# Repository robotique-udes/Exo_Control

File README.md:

# Exo_Control - ACE 2026

## Table of Contents

- [Our Team](#our-team)
- [Description](#description)
- [Project Overview](#project-overview)
- [Hardware](#hardware)
- [Getting Started](#getting-started)
- [Folder Overview](#folder-overview)
- [Development Notes](#development-notes)
- [License](#license)
- [Acknowledgments](#acknowledgments)
- [Authors](#authors)

## Our Team

## Description

**BioGenius** is a technical project within the Robotique UdeS group focused on designing a lightweight and powerful exoskeleton system. This system provides support to the legs, hips, and back, making walking and load handling easier. Our prototype helped the team secure first place at the Applied Collegiate Exoskeleton (ACE) Competition in the United States in both 2022 and 2023.

Founded in the fall of 2019 by two bioengineering enthusiasts, BioGenius has grown into a team of more than 10 members with expertise from several engineering disciplines. This project represents a pioneering effort at the undergraduate engineering level in Quebec.

This release corresponds to the code used for the **ACE 2026** competition at McMaster University.

<div style="text-align: center;">
  
</div>

## Hardware

The system is built around the following main hardware components:

- Microcontroller: Arduino ESP32 nano
- Inertial Measurement Units: BNO085
- Motor: CubemarsV2 AK10-9 KV100 and V3 AK10-9 KV60

## Getting Started

To get started with the project, clone the repository and build it with PlatformIO.

```bash
git clone https://github.com/robotique-udes/Exo_Control.git
cd Exo_Control
pio run
pio run -t upload
```

## Folder Overview

- [include](include): header files, class declarations, and shared configuration definitions
- [src](src): implementation files for the firmware, sensor handling, control logic, and motor control
- [docs](docs): development guidelines and supporting documentation
- [test](test): test-related files and future validation work
- [platformio.ini](platformio.ini): PlatformIO configuration for the embedded build

## Development Notes

The project follows the coding conventions documented in [docs/guideline/code_guideline.md](docs/guideline/code_guideline.md). In particular:

- use clear and descriptive names
- keep the code structure consistent
- document headers with Doxygen comments
- separate configuration, logic, and hardware interface concerns clearly

## License

Copyright (C) 2026,  Robotique UdeS

This program is free software: you can redistribute it and/or modify
it under the terms of the GNU General Public License as published by
the Free Software Foundation, either version 3 of the License, or
(at your option) any later version.

This program is distributed in the hope that it will be useful,
but WITHOUT ANY WARRANTY; without even the implied warranty of
MERCHANTABILITY or FITNESS FOR A PARTICULAR PURPOSE. See the
GNU General Public License for more details.

For more details, see <https://www.gnu.org/licenses/>.

## Acknowledgments

We invite you to explore the [Robotique UdeS website](https://robotiqueudes.ca/) to learn more about the team and discover other projects.

## Authors

The main contributors to the Exo_Control project are:

- Gabriel Desrochers
- Josseran-Pierre Gay
- Eloi Charbonneau
- Samuel Savaria
- Samuel Archambault
- Halima Bourdi
- Reem Youssef
- Édouard Moffet
- Jacob Turcotte
- Dannick Bilodeau
- Simon Trudeau
- Jorand Gagnon

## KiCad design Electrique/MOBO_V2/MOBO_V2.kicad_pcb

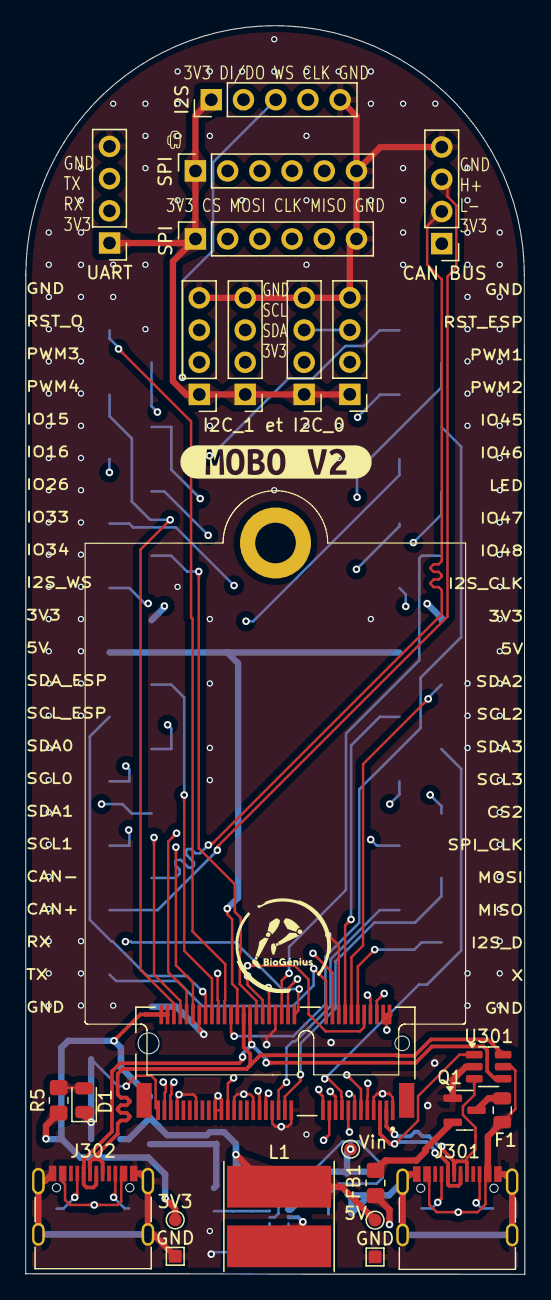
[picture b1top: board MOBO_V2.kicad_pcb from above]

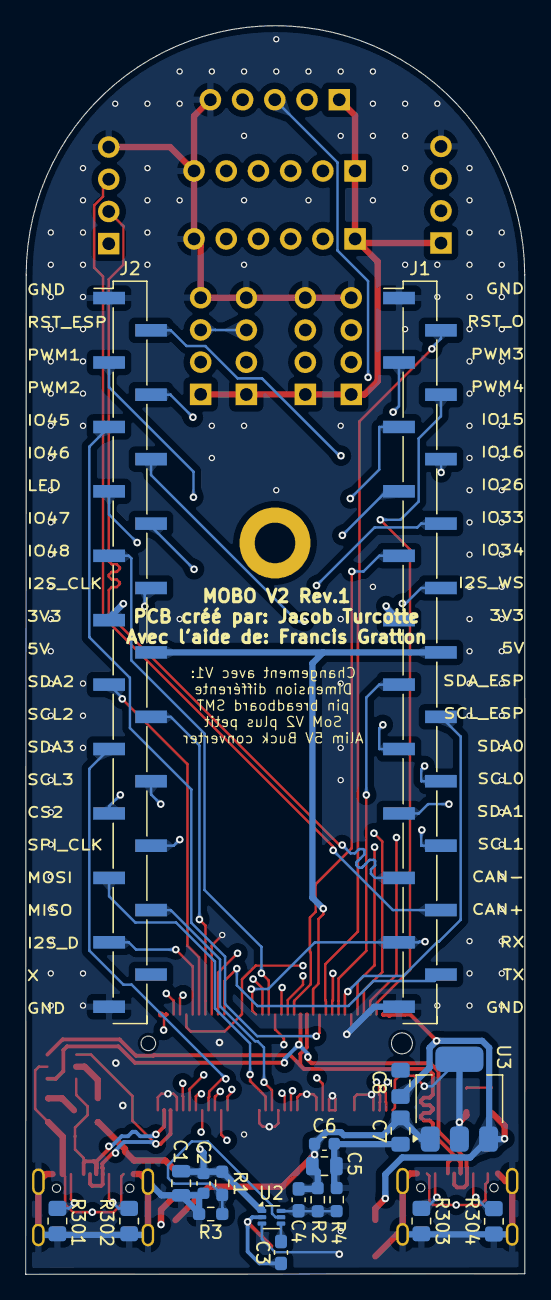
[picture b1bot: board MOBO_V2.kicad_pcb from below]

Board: 4 copper layers, 39.4 x 98.5 mm, 45 parts (20 on the bottom side), 58 nets.

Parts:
3V3: TP_3v3; TestPoint_Pad_D1.0mm
5V: TP_5V; TestPoint_Pad_D1.0mm
C1: 10µF; C_0805_2012Metric
C2, C6: 0,1µF; C_0603_1608Metric
C3: 0,1µF; C_0603_1608Metric_Pad1.08x0.95mm_HandSolder
C4: 33pF; C_0603_1608Metric_Pad1.08x0.95mm_HandSolder
C5: 22µF; C_0805_2012Metric
C7, C8: 4,7µF; C_0805_2012Metric_Pad1.18x1.45mm_HandSolder
CAN BUS: CAN_BUS; PinHeader_1x04_P2.54mm_Vertical
D1: Green_power; D_0805_2012Metric
F1: SMD0805B110TF; Fuse_0805_2012Metric
FB1: 600 @ 100MHz; R_0805_2012Metric_Pad1.20x1.40mm_HandSolder
GND: TP_GND; TestPoint_Pad_1.0x1.0mm
GND#2: TP_GND_IN; TestPoint_Pad_1.0x1.0mm
I2S: I2S; PinHeader_1x05_P2.54mm_Vertical
J1: Gauche; PinHeader_1x23_P2.54mm_Vertical_SMD_Pin1Left
J2: Droite; PinHeader_1x23_P2.54mm_Vertical_SMD_Pin1Left
J301: USB_C_UART; USB_C_Receptacle_G-Switch_GT-USB-7010ASV
J302: USB_C_DEBUG; USB_C_Receptacle_G-Switch_GT-USB-7010ASV
J307: I2C_0_0; PinHeader_1x04_P2.54mm_Vertical
J308: I2C_0_1; PinHeader_1x04_P2.54mm_Vertical
J309: I2C_1_0; PinHeader_1x04_P2.54mm_Vertical
J310: I2C_1_1; PinHeader_1x04_P2.54mm_Vertical
L1: 3,3µH 20mOhm; L_TDK_VLP8040
Q1: AO3401A; SOT-23
R1: 100k; R_0603_1608Metric_Pad0.98x0.95mm_HandSolder
R2: 158k; R_0603_1608Metric_Pad0.98x0.95mm_HandSolder
R3: 28k; R_0603_1608Metric_Pad0.98x0.95mm_HandSolder
R4: 30k; R_0603_1608Metric_Pad0.98x0.95mm_HandSolder
R5: 330; R_0805_2012Metric_Pad1.20x1.40mm_HandSolder
R301, R302, R303, R304: 5.1k; R_0805_2012Metric_Pad1.20x1.40mm_HandSolder
SPI: Conn_SPI; PinSocket_1x06_P2.54mm_Vertical
SPI#2: Conn_Module_SD; PinSocket_1x06_P2.54mm_Vertical
U1: AMPHENOL_MDT320E01001
U2: TPS562242DRLR; SOT-563
U3: AP7361C-33E; SOT-223-3_TabPin2
U301: SRV05-4; SOT-23-6
UART: UART; PinHeader_1x04_P2.54mm_Vertical
Vin: TP_VIN; TestPoint_Pad_D1.0mm
kibuzzard-66E82988: G***; kibuzzard-66E82988

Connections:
CAN_N: CAN BUS.2, J1.19, U1.73 (CAN_L_MCP2515)
CAN_P: CAN BUS.3, J1.20, U1.71 (CAN_H_MCP2515)
CHIP_EN: J2.2, U1.56 (RESET_ESP32)
CS_1: SPI#2.2, U1.20 (CS_1)
CS_2: J2.17, SPI.2, U1.21 (CS_2)
DEBUG_D+: J302.A6 (D+), J302.B6 (D+), U1.48 (USB_DEBUG_D+), U301.6 (IO4)
DEBUG_D-: J302.A7 (D-), J302.B7 (D-), U1.46 (USB_DEBUG_D-), U301.4 (IO3)
FT231_D+: J301.A6 (D+), J301.B6 (D+), U1.3 (USB_D+_FT231), U301.3 (IO2)
FT231_D-: J301.A7 (D-), J301.B7 (D-), U1.5 (USB_D-_FT231), U301.1 (IO1)
GND: C1.2, C2.2, C5.2, C6.2, C7.1, C8.1, CAN BUS.4, D1.1 (K), GND.1, GND#2.1, I2S.5, J1.1, J1.23, J2.1, J2.23, J301.A1 (GND), J301.A12 (GND), J301.B1 (GND), J301.B12 (GND), J301.S1 (SHIELD), J302.A1 (GND), J302.A12 (GND), J302.B1 (GND), J302.B12 (GND), J302.S1 (SHIELD), J307.4, J308.4, J309.4, J310.4, Q1.1 (G), R3.2, R4.2, R301.2, R302.2, R303.2, R304.2, SPI.6, SPI#2.6, U1.1 (GND), U1.7 (GND), U1.18 (GND), U1.33 (GND), U1.38 (GND), U1.39 (GND), U1.45 (GND), U1.51 (GND), U1.55 (GND), U1.57 (GND), U1.62 (GND), U1.63 (GND), U1.69 (GND), U1.75 (GND), U2.3 (GND), U3.2 (GND), U301.2 (VN), UART.4
GPIO15: J1.5, U1.40 (GPIO15)
GPIO16: J1.6, U1.41 (GPIO16)
GPIO17_U1_TXD: J1.22, U1.22 (UART_TX), UART.3
GPIO18_U1_RXD: J1.21, U1.32 (UART_RX), UART.2
GPIO26: J1.7, U1.42 (GPIO26)
GPIO33: J1.8, U1.43 (GPIO33)
GPIO34: J1.9, U1.44 (GPIO34)
GPIO38_ADDRESSABLE_LED: J2.7, U1.6 (GPIO38&LED)
GPIO45: J2.5, U1.52 (GPIO45)
GPIO46: J2.6, U1.53 (GPIO46)
GPIO47: J2.8, U1.34 (RST_OTHER)
GPIO48/CAN_INT: J2.9, U1.36 (GPIO48)
I2C_SCL_0_TCA: J1.16, J307.3, J308.3, U1.11 (I2C_SCL_1_TCA)
I2C_SCL_1_TCA: J1.18, J309.3, J310.3, U1.15 (I2C_SCL_2_TCA)
I2C_SCL_2_TCA: J2.14, U1.16 (I2C_SCL_3_TCA)
I2C_SCL_3_TCA: J2.16, U1.19 (I2C_SCL_4_TCA)
I2C_SCL_ESP32: J1.14, U1.60 (I2C_SCL_ESP32)
I2C_SDA_0_TCA: J1.15, J307.2, J308.2, U1.9 (I2C_SDA_1_TCA)
I2C_SDA_1_TCA: J1.17, J309.2, J310.2, U1.13 (I2C_SDA_2_TCA)
I2C_SDA_2_TCA: J2.13, U1.14 (I2C_SDA_3_TCA)
I2C_SDA_3_TCA: J2.15, U1.17 (I2C_SDA_4_TCA)
I2C_SDA_ESP32: J1.13, U1.58 (I2C_SDA_ESP32)
I2S_BCLK: I2S.4, J2.10, U1.8 (I2S_BCLK)
I2S_DIN/DOUT: I2S.2, J2.21, U1.12 (I2S_DIN/DOUT)
I2S_WS: I2S.3, J1.10, U1.10 (I2S_WS)
unnamed: D1.2 (A), R5.2
unnamed: J301.A5 (CC1), R302.1
unnamed: J301.B5 (CC2), R301.1
unnamed: J302.A5 (CC1), R304.1
unnamed: J302.B5 (CC2), R303.1
unnamed: F1.2, Q1.3 (D)
unnamed: FB1.1, Q1.2 (S)
unnamed: R1.2, R3.1, U2.5 (EN)
unnamed: C3.1, L1.1, U2.2 (SW)
unnamed: C3.2, U2.4 (VBST)
unnamed: C4.2, R2.2, R4.1, U2.6 (VFB)
PWM_1: J2.3, U1.64 (PWM_1_PCA)
PWM_2: J2.4, U1.66 (PWM_2_PCA)
PWM_3: J1.3, U1.68 (PWM_3_PCA)
PWM_4: J1.4, U1.70 (PWM_4_PCA)
RESET_OTHERS: J1.2, U1.54 (RESET_AUTRES)
SPI_CLK_ESP32: J2.18, SPI.4, SPI#2.4, U1.23 (SPI_CLK)
SPI_MISO_ESP32: J2.20, SPI.5, SPI#2.5, U1.37 (SPI_MISO)
SPI_MOSI_ESP32: J2.19, SPI.3, SPI#2.3, U1.35 (SPI_MOSI)
VBUS: F1.1, J301.A4 (VBUS), J301.A9 (VBUS), J301.B4 (VBUS), J301.B9 (VBUS), J302.A4 (VBUS), J302.A9 (VBUS), J302.B4 (VBUS), J302.B9 (VBUS), U301.5 (VP)
VIN_PROTECTION: C1.1, C2.1, FB1.2, R1.1, U2.1 (VIN), Vin.1
Vcc_3V3: 3V3.1, C8.2, CAN BUS.1, I2S.1, J1.11, J2.11, J307.1, J308.1, J309.1, J310.1, R5.1, SPI.1, SPI#2.1, U1.2 (Vcc_3v3), U1.4 (Vcc_3v3), U1.72 (Vcc_3v3), U1.74 (Vcc_3v3), U3.3 (VO), UART.1
Vcc_5V: 5V.1, C4.1, C5.1, C6.1, C7.2, J1.12, J2.12, L1.2, R2.1, U1.50 (Vcc_5V), U3.1 (VI)

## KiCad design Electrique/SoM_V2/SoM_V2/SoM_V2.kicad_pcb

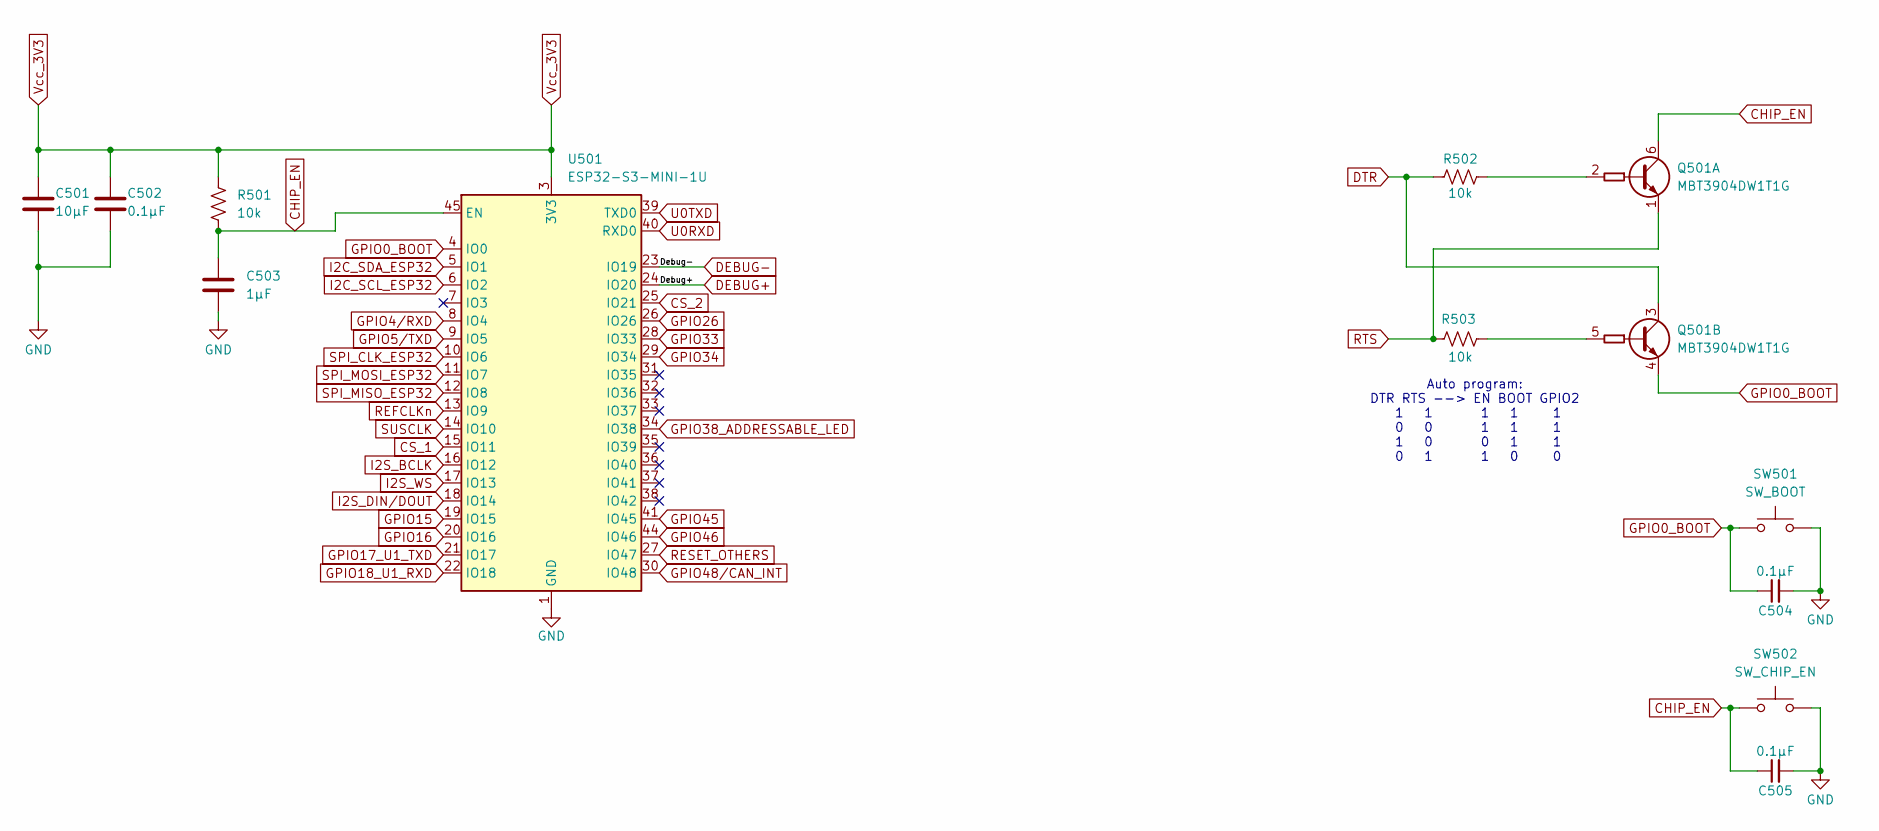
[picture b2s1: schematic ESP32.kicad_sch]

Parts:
C501: 10µF; R_0805_2012Metric
C502, C504, C505: 0.1µF; R_0805_2012Metric
C503: 1µF; R_0805_2012Metric
Q501: MBT3904DW1T1G; SOT-363_SC-70-6
R501, R502, R503: 10k; R_0805_2012Metric
SW501: SW_BOOT; SW_DIP_SPSTx01_Slide_6.7x4.1mm_W6.73mm_P2.54mm_LowProfile_J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
SW502: SW_CHIP_EN; SW_DIP_SPSTx01_Slide_6.7x4.1mm_W6.73mm_P2.54mm_LowProfile_J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
U501: ESP32-S3-MINI-1U; ESP32-S2-MINI-1U

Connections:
CHIP_EN: C503.1, C505.1, Q501.6 (C1), R501.2, SW502.1, U501.45 (EN); also elsewhere on the board
CS_1: U501.15 (IO11); also elsewhere on the board
CS_2: U501.25 (IO21); also elsewhere on the board
DEBUG+: U501.24 (IO20); also elsewhere on the board
DEBUG-: U501.23 (IO19); also elsewhere on the board
DTR: Q501.3 (C2), R502.1; also elsewhere on the board
GPIO0_BOOT: C504.1, Q501.4 (E2), SW501.1, U501.4 (IO0)
GPIO4/RXD: U501.8 (IO4); also elsewhere on the board
GPIO5/TXD: U501.9 (IO5); also elsewhere on the board
GPIO15: U501.19 (IO15); also elsewhere on the board
GPIO16: U501.20 (IO16); also elsewhere on the board
GPIO17_U1_TXD: U501.21 (IO17); also elsewhere on the board
GPIO18_U1_RXD: U501.22 (IO18); also elsewhere on the board
GPIO26: U501.26 (IO26); also elsewhere on the board
GPIO33: U501.28 (IO33); also elsewhere on the board
GPIO34: U501.29 (IO34); also elsewhere on the board
GPIO38_ADDRESSABLE_LED: U501.34 (IO38); also elsewhere on the board
GPIO45: U501.41 (IO45); also elsewhere on the board
GPIO46: U501.44 (IO46); also elsewhere on the board
GPIO48/CAN_INT: U501.30 (IO48); also elsewhere on the board
I2C_SCL_ESP32: U501.6 (IO2); also elsewhere on the board
I2S_BCLK: U501.16 (IO12); also elsewhere on the board
I2S_DIN/DOUT: U501.18 (IO14); also elsewhere on the board
I2S_WS: U501.17 (IO13); also elsewhere on the board
unnamed: Q501.2 (B1), R502.2
unnamed: Q501.5 (B2), R503.2
REFCLKn: U501.13 (IO9)
RESET_OTHERS: U501.27 (IO47); also elsewhere on the board
RTS: Q501.1 (E1), R503.1; also elsewhere on the board
SPI_CLK_ESP32: U501.10 (IO6); also elsewhere on the board
SPI_MISO_ESP32: U501.12 (IO8); also elsewhere on the board
SPI_MOSI_ESP32: U501.11 (IO7); also elsewhere on the board
SUSCLK: U501.14 (IO10)
U0RXD: U501.40 (RXD0); also elsewhere on the board
U0TXD: U501.39 (TXD0); also elsewhere on the board

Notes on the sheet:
Auto program: DTR RTS --> EN BOOT GPIO2 1 1 1 1 1 0 0 1 1 1 1 0 0 1 1 0 1 1 0 0

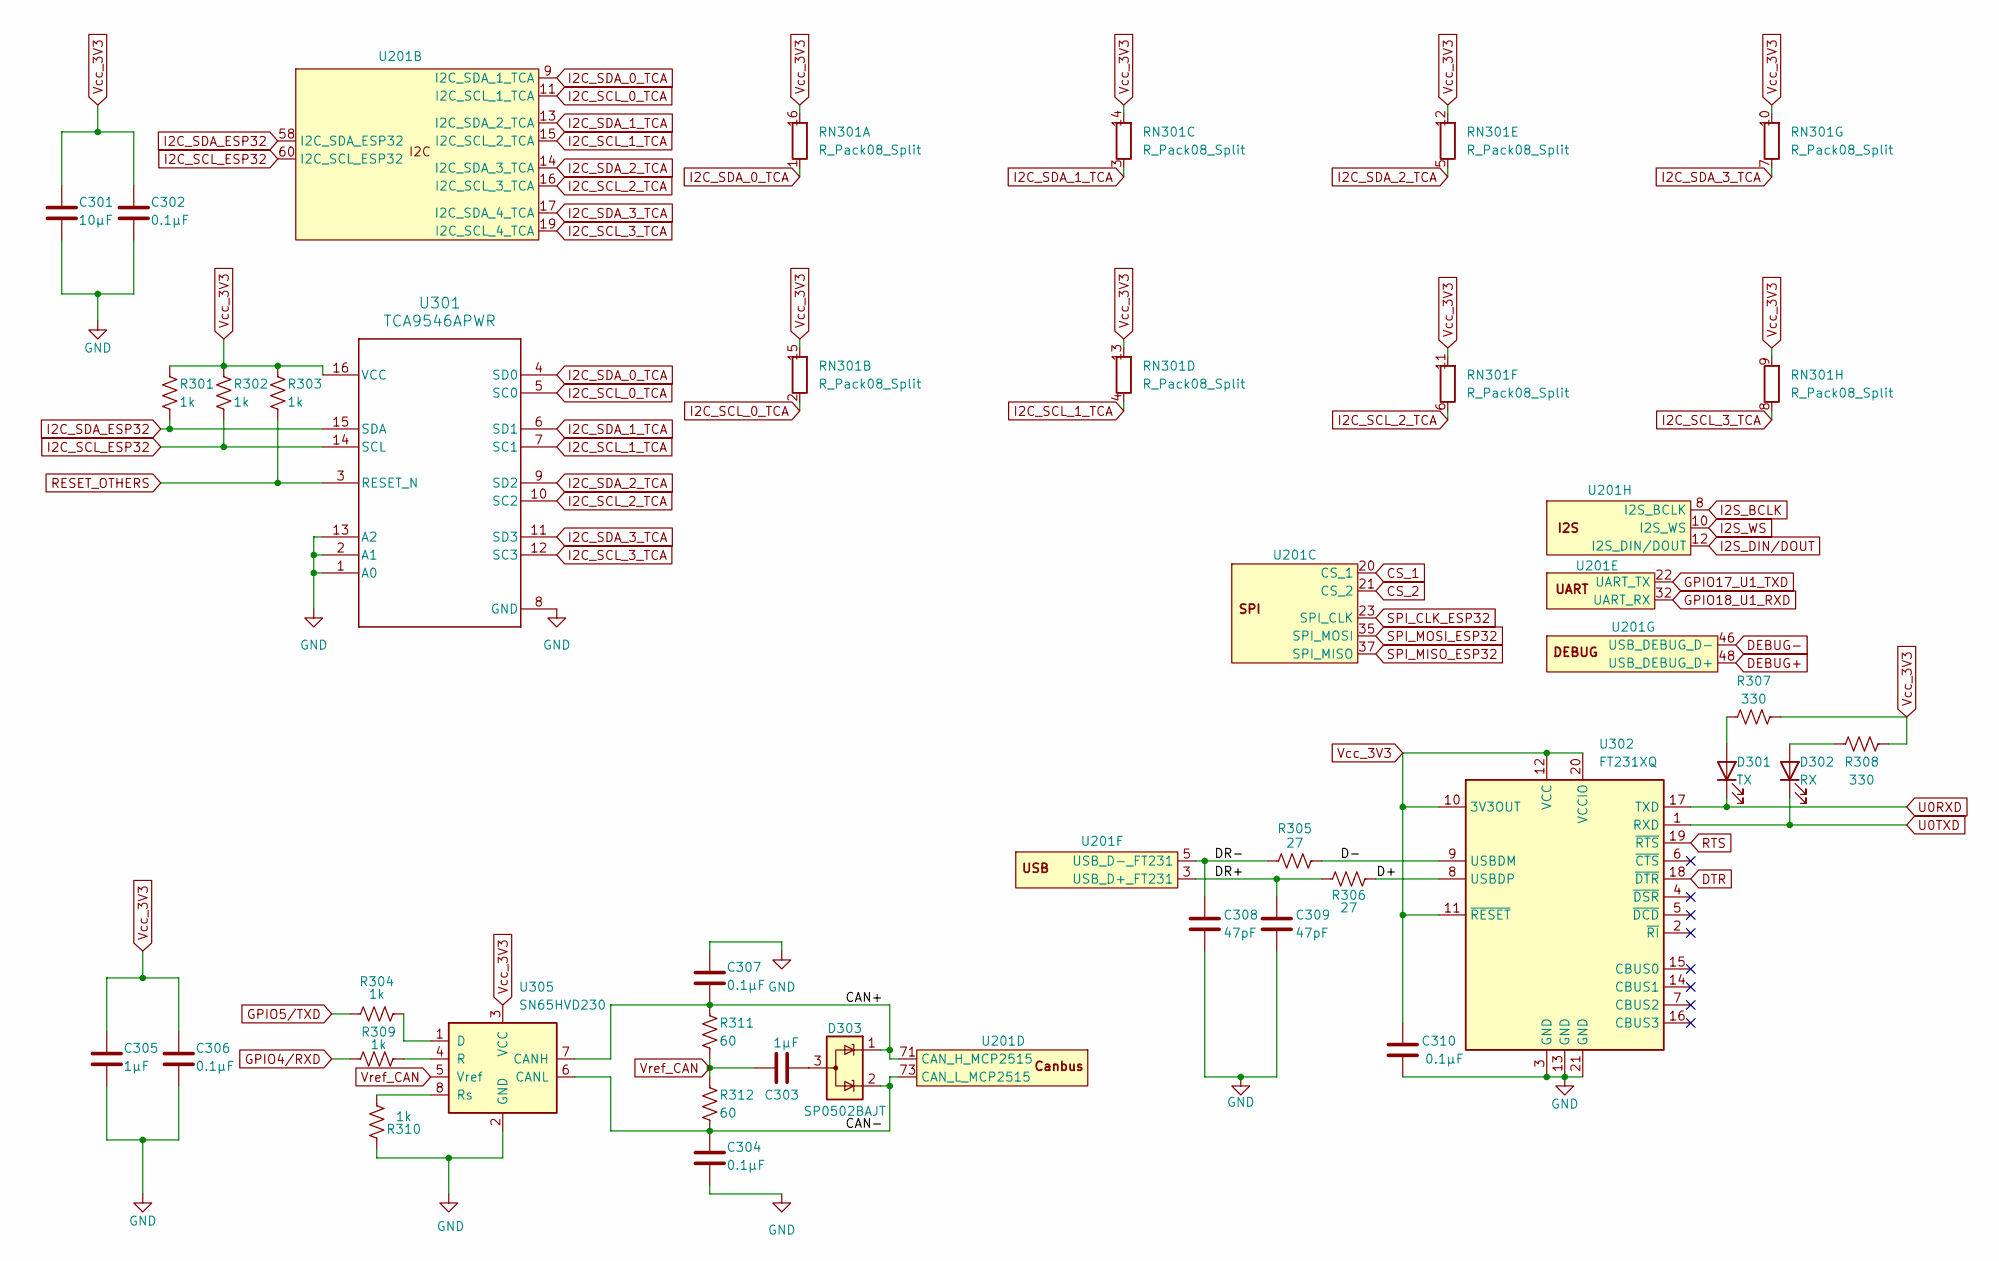
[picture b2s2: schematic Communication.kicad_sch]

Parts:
C301: 10µF; R_0805_2012Metric
C302, C304, C306, C307, C310: 0.1µF; R_0805_2012Metric
C303, C305: 1µF; R_0805_2012Metric
C308, C309: 47pF; R_0805_2012Metric
D301: TX; LED_0805_2012Metric
D302: RX; LED_0805_2012Metric
D303: SP0502BAJT; SOT-323_SC-70
R301, R302, R303, R304, R309, R310: 1k; R_0805_2012Metric
R305, R306: 27; R_0805_2012Metric
R307, R308: 330; R_0805_2012Metric
R311, R312: 60; R_0805_2012Metric
RN301: R_Pack08_Split; R_Array_Convex_8x0602
U201: NGFF_E
U301: TCA9546APWR; TSSOP-16_4.4x5mm_P0.65mm
U302: FT231XQ; QFN-20-1EP_4x4mm_P0.5mm_EP2.5x2.5mm
U305: SN65HVD230; SOIC-8_3.9x4.9mm_P1.27mm

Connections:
/Communication/CAN+: C307.2, D303.1 (K), R311.1, U201.71 (CAN_H_MCP2515), U305.7 (CANH)
/Communication/CAN-: C304.1, D303.2 (K), R312.2, U201.73 (CAN_L_MCP2515), U305.6 (CANL)
/Communication/D+: R306.2, U302.8 (USBDP)
/Communication/D-: R305.2, U302.9 (USBDM)
/Communication/DR+: C309.1, R306.1, U201.3 (USB_D+_FT231)
/Communication/DR-: C308.1, R305.1, U201.5 (USB_D-_FT231)
CS_1: U201.20 (CS_1); also elsewhere on the board
CS_2: U201.21 (CS_2); also elsewhere on the board
DEBUG+: U201.48 (USB_DEBUG_D+); also elsewhere on the board
DEBUG-: U201.46 (USB_DEBUG_D-); also elsewhere on the board
DTR: U302.18 (~DTR); also elsewhere on the board
GPIO4/RXD: R309.1; also elsewhere on the board
GPIO5/TXD: R304.1; also elsewhere on the board
GPIO17_U1_TXD: U201.22 (UART_TX); also elsewhere on the board
GPIO18_U1_RXD: U201.32 (UART_RX); also elsewhere on the board
I2C_SCL_0_TCA: RN301.2 (R2.1), U201.11 (I2C_SCL_1_TCA), U301.5 (SC0)
I2C_SCL_1_TCA: RN301.4 (R4.1), U201.15 (I2C_SCL_2_TCA), U301.7 (SC1)
I2C_SCL_2_TCA: RN301.6 (R6.1), U201.16 (I2C_SCL_3_TCA), U301.10 (SC2)
I2C_SCL_3_TCA: RN301.8 (R8.1), U201.19 (I2C_SCL_4_TCA), U301.12 (SC3)
I2C_SCL_ESP32: R302.2, U201.60 (I2C_SCL_ESP32), U301.14 (SCL); also elsewhere on the board
I2C_SDA_0_TCA: RN301.1 (R1.1), U201.9 (I2C_SDA_1_TCA), U301.4 (SD0)
I2C_SDA_1_TCA: RN301.3 (R3.1), U201.13 (I2C_SDA_2_TCA), U301.6 (SD1)
I2C_SDA_2_TCA: RN301.5 (R5.1), U201.14 (I2C_SDA_3_TCA), U301.9 (SD2)
I2C_SDA_3_TCA: RN301.7 (R7.1), U201.17 (I2C_SDA_4_TCA), U301.11 (SD3)
I2S_BCLK: U201.8 (I2S_BCLK); also elsewhere on the board
I2S_DIN/DOUT: U201.12 (I2S_DIN/DOUT); also elsewhere on the board
I2S_WS: U201.10 (I2S_WS); also elsewhere on the board
unnamed: D301.2 (A), R307.1
unnamed: D302.2 (A), R308.1
unnamed: C303.2, D303.3 (A)
unnamed: R304.2, U305.1 (D)
unnamed: R309.2, U305.4 (R)
unnamed: R310.2, U305.8 (Rs)
RESET_OTHERS: R303.2, U301.3 (RESET_N); also elsewhere on the board
RTS: U302.19 (~RTS); also elsewhere on the board
SPI_CLK_ESP32: U201.23 (SPI_CLK); also elsewhere on the board
SPI_MISO_ESP32: U201.37 (SPI_MISO); also elsewhere on the board
SPI_MOSI_ESP32: U201.35 (SPI_MOSI); also elsewhere on the board
U0RXD: D301.1 (K), U302.17 (TXD); also elsewhere on the board
U0TXD: D302.1 (K), U302.1 (RXD); also elsewhere on the board
Vref_CAN: C303.1, R311.2, R312.1, U305.5 (Vref)

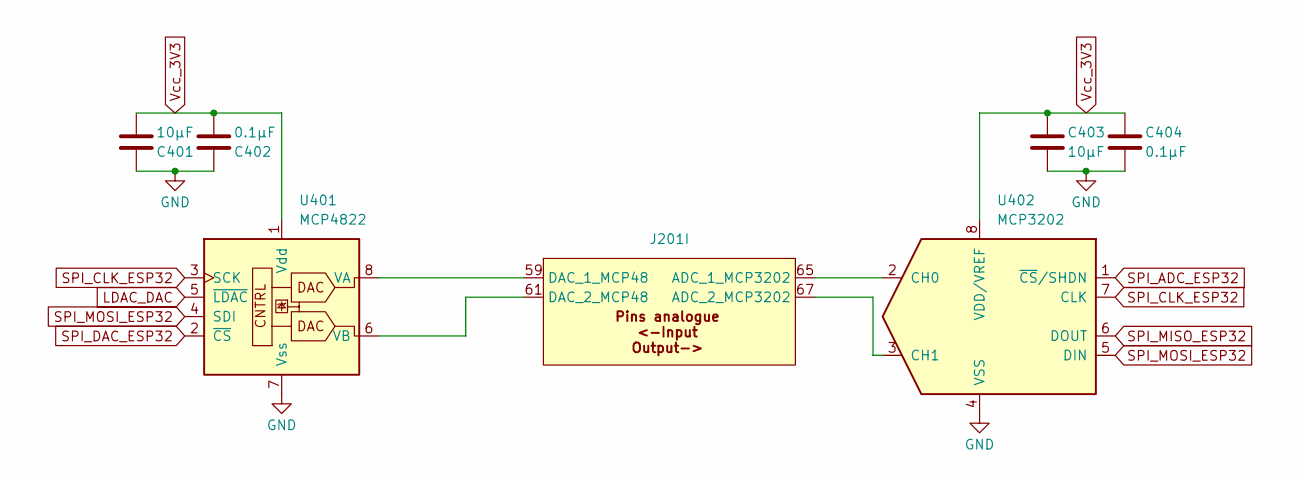
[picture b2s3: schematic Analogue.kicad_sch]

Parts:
C401, C403: 10µF; R_0805_2012Metric
C402, C404: 0.1µF; R_0805_2012Metric
J201: NGFF_E
U401: MCP4822; SOIC-8_3.9x4.9mm_P1.27mm
U402: MCP3202; SOIC-8_3.9x4.9mm_P1.27mm

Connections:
I2C_SCL_ESP32: J201.61 (DAC_2_MCP48), U401.6 (SCL6); also elsewhere on the board
unnamed: J201.65 (ADC_1_MCP3202), U402.2 (CH0)
unnamed: J201.67 (ADC_2_MCP3202), U402.3 (CH1)
unnamed 46: U401.2 (PWM2); also elsewhere on the board
unnamed 47: U401.3 (PWM3), U402.7 (CLK); also elsewhere on the board
unnamed 48: U401.4 (PWM4), U402.5 (DIN); also elsewhere on the board

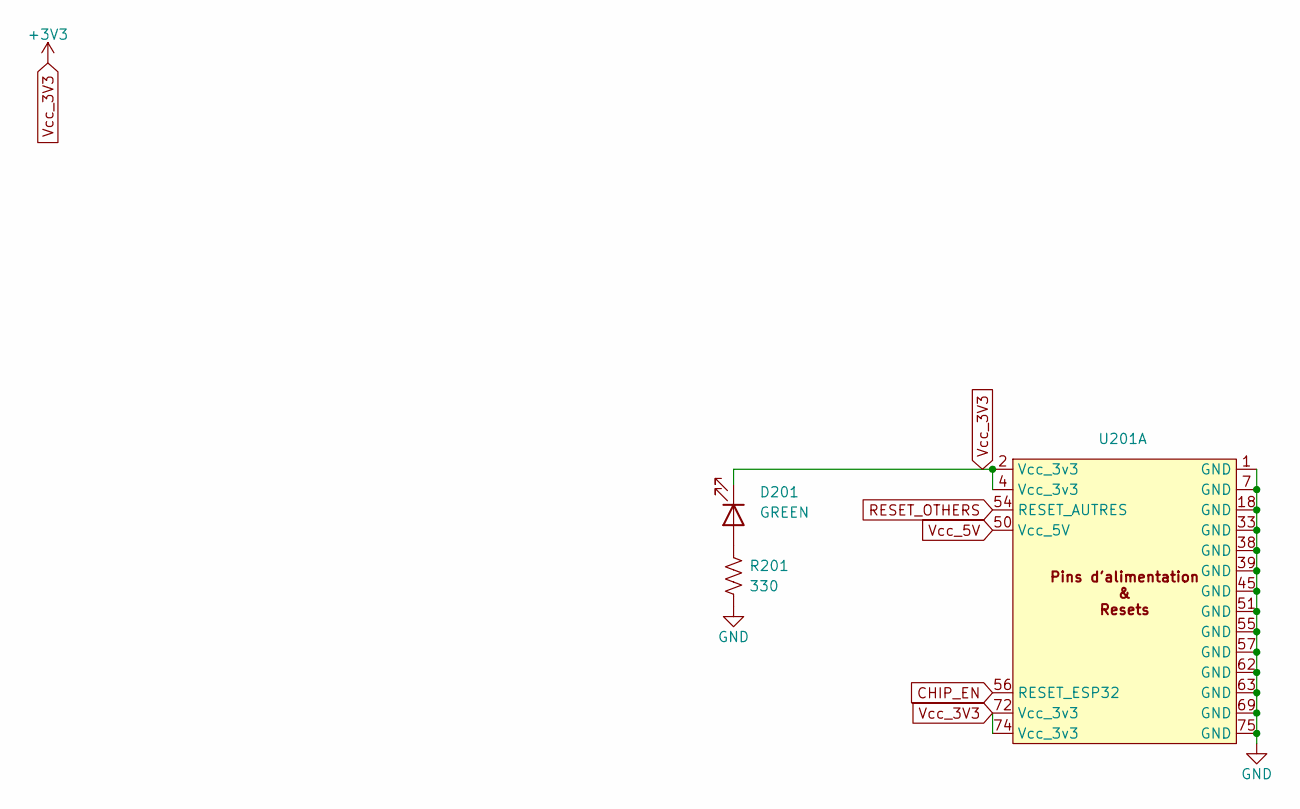
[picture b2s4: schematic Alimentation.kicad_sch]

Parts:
D201: GREEN; LED_0805_2012Metric
R201: 330; R_0805_2012Metric
U201: NGFF_E

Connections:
CHIP_EN: U201.56 (RESET_ESP32); also elsewhere on the board
unnamed: D201.2 (A), R201.1
RESET_OTHERS: U201.54 (RESET_AUTRES); also elsewhere on the board
Vcc_5V: U201.50 (Vcc_5V)

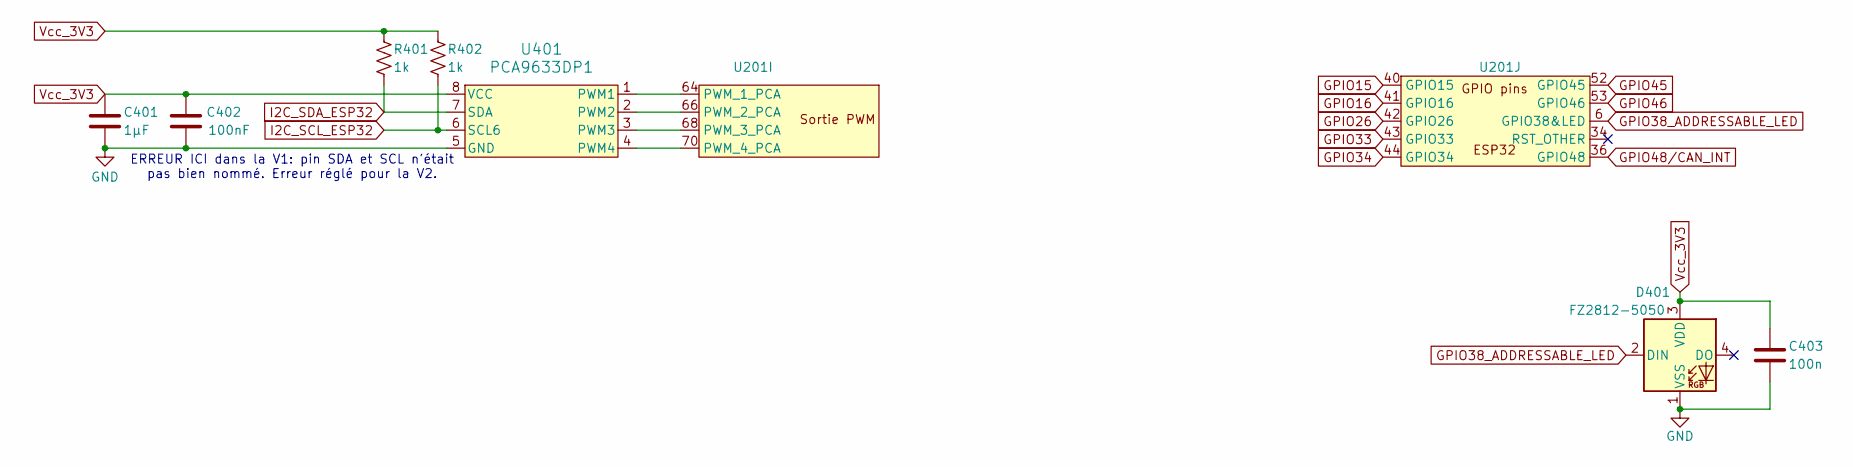
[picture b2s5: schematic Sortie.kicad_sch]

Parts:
C401: 1µF; R_0805_2012Metric
C402: 100nF; R_0805_2012Metric
C403: 100n; C_0805_2012Metric
D401: FZ2812-5050; LED_Inolux_IN-PI554FCH_PLCC4_5.0x5.0mm_P3.2mm
R401, R402: 1k; R_0805_2012Metric
U201: NGFF_E
U401: PCA9633DP1; DFN-8-1EP_2x2mm_P0.5mm_EP0.9x1.6mm

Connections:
GPIO15: U201.40 (GPIO15); also elsewhere on the board
GPIO16: U201.41 (GPIO16); also elsewhere on the board
GPIO26: U201.42 (GPIO26); also elsewhere on the board
GPIO33: U201.43 (GPIO33); also elsewhere on the board
GPIO34: U201.44 (GPIO34); also elsewhere on the board
GPIO38_ADDRESSABLE_LED: D401.2 (DIN), U201.6 (GPIO38&LED); also elsewhere on the board
GPIO45: U201.52 (GPIO45); also elsewhere on the board
GPIO46: U201.53 (GPIO46); also elsewhere on the board
GPIO48/CAN_INT: U201.36 (GPIO48); also elsewhere on the board
I2C_SCL_ESP32: R402.2, U401.6 (SCL6); also elsewhere on the board
unnamed: U201.66 (PWM_2_PCA), U401.2 (PWM2)
unnamed 47: U201.68 (PWM_3_PCA), U401.3 (PWM3); also elsewhere on the board
unnamed 48: U201.70 (PWM_4_PCA), U401.4 (PWM4); also elsewhere on the board

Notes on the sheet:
ERREUR ICI dans la V1: pin SDA et SCL n'était pas bien nommé. Erreur réglé pour la V2.

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
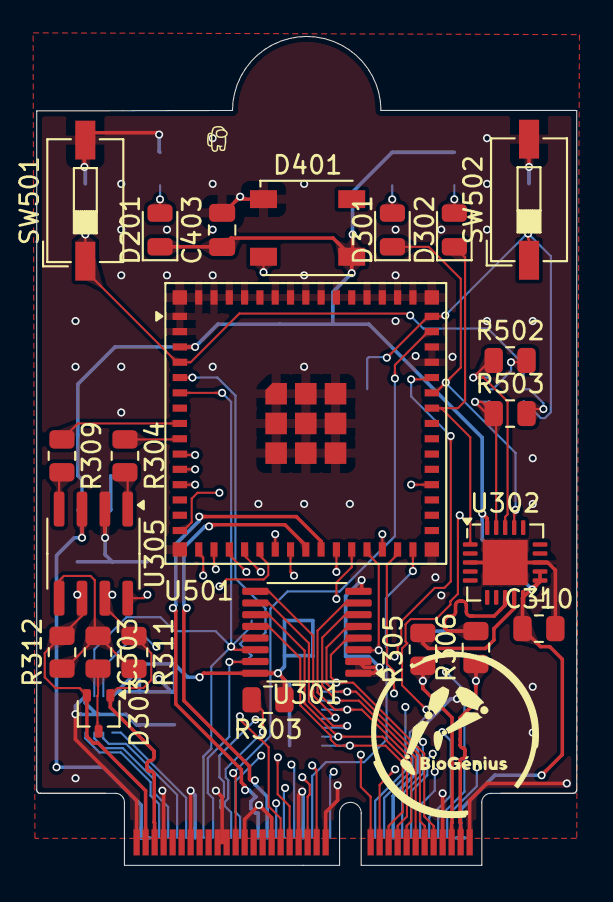
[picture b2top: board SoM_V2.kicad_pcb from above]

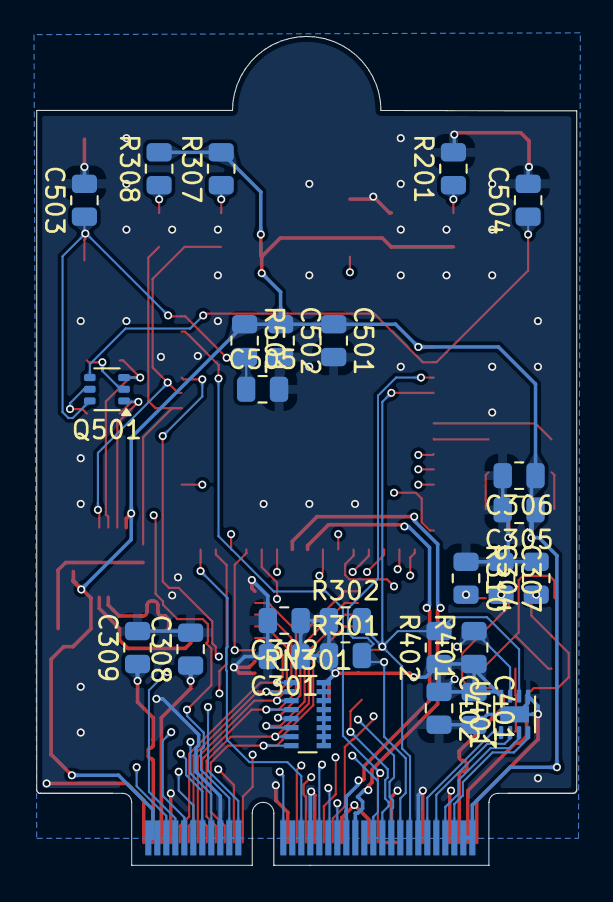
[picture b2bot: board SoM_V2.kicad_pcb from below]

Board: 4 copper layers, 30.0 x 46.1 mm, 51 parts (27 on the bottom side), 62 nets.

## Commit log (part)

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2024-05-10 Fix HMI
2024-05-10 pwm fonctionel
2024-05-10 Clean code
2024-05-13 Code compiles, fixing errors
2024-05-13 Add encoders. To be tested
2024-05-14 Changes to proxim integration
2024-05-15 Integration
    Début de l'intégration du HMI, besoin d'intégrer avec le GPIO extender et de tester ensuite avant de merge
2024-05-16 Fix bugs in motorcontrol. Encoder working in test code, but to be debbuged in class
2024-05-17 fix de l'incrémentation des encodeurs dans leur classe
2024-05-20 Added prints and changed name
2024-05-20 Github being weird as fuck
2024-05-20 Single talking through MUX
2024-05-20 Cleanup BNO class
2024-05-21 Déplacement du keyboard command dans le tester
2024-05-21 Fix encoder angles
2024-05-22 Début logique toggle IMU/Encoder
2024-05-22 Hotswappable BNO
2024-05-22 BNOs accessible through IMU
2024-05-22 IMU fully implemented
2024-05-22 Fix enumIMU conflicts
2024-05-22 Try IMUs
2024-05-22 BNOs print on exo!
2024-05-23 Integration IMU dos
2024-05-23 Added Multiplexer to proxim
2024-05-23 Fix minor display issue
2024-05-23 New HMI callbacks
2024-05-23 proxim buffer
2024-05-24 Init et define buffer
2024-05-24 lmao rolf kekw
2024-05-24 Added back angle
2024-05-24 Fix torque equations
2024-05-24 HMI panic shenanigans
2024-05-24 Fix motor direction and uncomment logic in main
2024-05-24 fix herp derp des proxim
2024-05-25 proxim fixed? (copium)
2024-05-25 proxy poggers (slight cope)
2024-05-25 kfdffdfyguliyiouilukhgjyfhgd
2024-05-25 Add scrolling logs
2024-05-25 V1 of assisted PWM
2024-05-25 it would be cool if my code compiles
2024-05-25 settings modifs
2024-05-25 brightness
2024-05-25 Added prints
2024-05-25 Working code when broken leg
2024-05-25 proxim toggle
2024-06-07 Integration of new imu methods for wifi simulation
2024-06-18 Simulation tested and working. Change from joint angles to direct angles (tibia, thigh)
2024-06-18 Initial
2024-06-18 Old classed and cleaned code
2024-06-19 refactor compute angles
2024-06-25 enums refactor and wifi fucking up fix
2024-06-29 📝 Added docstring for IMU
2024-06-29 proximHandler
2024-06-29 Rename structs
2024-06-29 Rename BNO related classes
2024-07-09 push connecteur
2024-07-14 Quadratur encoder refoctoring
2024-07-24 motor and logic class added
2024-07-24 cleaned a few things
2024-07-30 docstrings
2024-08-07 PR review fixes
2024-08-07 upload X and Z IMU detection to the wifi
2024-08-19 Edouarder le code
2024-08-19 Angles accessible for joint and for body parts
2024-08-24 Push de 3 nouveau board/PCB
2024-08-31 New torque equations and refactor. To test
2024-09-03 push pour frank
2024-09-03 push fix background
2024-09-03 stinky kicad
2024-09-07 moving vars
2024-09-07 Semi BNOstruct in dataCore, print linacceleration
2024-09-07 push v2.2
2024-09-07 logout kicasd
2024-09-10 Clean up schema et PCB
2024-09-10 humpty dumpty dumbspter truck
2024-09-10 Some Details about Schematics
2024-09-11 BNOStruct accessible in datacore
2024-09-11 Some modif of traces
2024-09-13 upload mobo v2 pcb
2024-09-16 PCB terminé en attente de vérification
2024-09-18 verified by frank
2024-10-05 Fixed oopsy doopsy
2024-10-05 Better integration between math and detect ground
2024-10-16 Start new project wifi server
2024-10-25 seeing the reel message
2024-10-27 Add c_cpp_properties.json for Visual Studio Code configuration
2024-11-06 started refactoring
2024-11-07 Refactor WiFi communication by creating WifiClient class and separating UDP functionality
2024-11-07 Update WiFiClient configuration and improve connection handling
2024-11-13 class server
2024-11-13 Refactor WifiClient initialization and move Wi-Fi connection to setup function
2024-11-14 No more night terror
    proxim be gone
2024-11-14 cleanup
2024-11-20 Refactor WifiClient to support IP address management and enhance message sending functionality
2024-11-20 messagebuilder
2024-11-21 Refactor WifiClient to replace ArduinoJson with MessageBuilder and enhance message handling
2024-12-04 fixed path problem
2024-12-05 Enums in Libs
2024-12-05 Enhance MessageBuilder with clearInfo method and update enums for better state representation
2024-12-05 Code does not work, but is in commentary
2024-12-05 Refactor WifiClient and MessageBuilder: update enum types for IP handling and enhance message construction
2024-12-05 Fix MessageBuilder: add serialization of JSON document in buildMessage function
2025-01-03 Enhance WifiClient: add dynamic data size calculation and error handling in sendMessage function
2025-01-03 Fix include formatting and clean up build flags in platformio.ini files
2025-01-06 push pull up sur reset et prog
2025-01-08 Add MessageBuilder class for structured message handling and logging
2025-01-09 trust the singleton
2025-01-15 some stuff will need to fix hand shake
2025-01-16 does not work
2025-01-16 it works
2025-01-16 Revert "int length"
    This reverts commit 3d4a3bbb3624dffd512a3b5e32c50e8ce827d02d.
2025-01-19 Building libs from another folder
2025-01-22 Started implementing the dictionary
2025-01-23 Add logging functionality to message building process
2025-01-26 well that sucks
2025-01-27 Should all be working now
2025-01-29 ready to integrate it
2025-01-29 Refactor handshake process and add message deserialization functionality
2025-01-30 Update message deserialization to return a map and enhance VSCode settings for C++ file associations
2025-01-30 Refactor message deserialization to use string values and update IP address handling in WifiClient and WifiServer
2025-02-02 fixed some problems
2025-02-04 simplified code
2025-02-05 trust, il y a quelque bug
2025-02-05 return length
2025-02-06 Enhance WifiClient functionality by adding data length handling in message processing and improving packet reception logic
2025-02-08 Add debug prints for IP address and modify UDP packet destination in WifiClient and WifiServer
2025-02-11 going to test tomorrow
2025-02-13 ip works
2025-02-13 forgot message builder
2025-02-13 there were some changes not wanted
2025-02-13 fix main
2025-02-17 com works, will need to make more defines for the nestedArrays
2025-02-19 Added the ability to know what the client is. Kneed to test it
2025-02-24 Communication works, still need to implement the rest
2025-02-27 Changes conversions char dans message builder
2025-02-27 Enhance message sending with debug output and correct data length usage
2025-02-27 Refactor MessageBuilder::add method to accept const char* and update related implementations
2025-03-01 MotorHandler base added
2025-03-03 Implement singleton pattern for WifiClient and enhance connection handling
2025-03-06 Improve WifiClient message handling by checking data availability before receiving messages
2025-03-19 Test moteur
2025-03-26 petite modification
2025-03-26 Add initial project structure with configuration and documentation files
2025-04-02 compiling
2025-04-02 Fix handshake condition in WifiClient to ensure it only triggers when connected
2025-04-02 Add digital clock example using TFT LCD display
2025-04-06 Add PlatformIO configuration and initial library structure for WifiCommunication and Watch HMI
2025-04-13 okok i guess
2025-04-14 The start with LVGL
2025-04-14 good enough i guess
2025-04-16 looking ok i guess
2025-04-21 lots of updates, can send some values between watch and exo
2025-04-21 auto reconnect
2025-04-25 Refactor HMI class and setup methods; add style initialization and exo settings UI elements
2025-04-25 Update HMI structure and add background setup; modify tile assignments for exo settings and menu
2025-04-26 Enhance HMI functionality: add charge mass and height controls, refactor setup methods, and improve connection status updates
2025-05-07 Refactor HMI class: update default values, add mass/charge/height control methods, and implement event handlers for UI interactions
2025-05-07 Add SAE/SI toggle and reset functionality to HMI; update UI elements and event handlers
2025-05-07 Add CHARGE_MASSE to EnumInformations for enhanced data representation
2025-05-07 Is exo connected
2025-05-07 Refactor HMI setup: update slider dimensions, adjust label positions, and correct height unit conversion
2025-05-08 Fix loop condition in buildMessage to iterate over indexStructInformations instead of indexStructMotorPosition
2025-05-08 Add motor power functionality to HMI: initialize default value, update label, and handle slider events
2025-05-15 compiles
2025-05-22 started the inheritence of the motor class
2025-05-28 polymorphism implemented in motorhandler
2025-06-02 first part of v3 code
2025-06-04 test for today
2025-06-04 equation dynamique ajouté
    pas encode testé tho
2025-06-10 v3 update
2025-06-10 main ready for test
2025-06-16 V3 good
2025-07-09 test mobo
2026-01-22 v3 working with mobo
2026-01-24 v2 working with mobo
2026-01-24 V3 temperature reading done
2026-01-28 Added platform_packages option to PlatformIO's config
2026-03-05 Ignore .pio folder for WifiClient and WifiServer
2026-03-05 Added platform package to make compilation work
2026-03-05 Added empty markdown files for documentation
2026-03-05 Added ignore of files inside .vscode/
2026-03-05 Corrected include path
2026-03-05 Just added empty .vscode/ folder. Ignore
2026-03-28 Fixed pin compatibility with Arduino Nano ESP32
2026-04-04 Ignore
2026-04-08 now works with modif to adafruit library (to be forked)
2026-04-08 new lib to modify max instance
2026-04-15 ai refact test
2026-04-21 move legacy code and define some magic number
2026-04-21 doc for bnoHandler and some more cleanup, moved non-bno angle out of bnohandler method to logic
2026-04-23 fixed ; macro issue
2026-04-29 BNO working with sparkfun library
2026-04-29 Changed name of folders to reflect bluetooth use
2026-04-29 remove dataCore
2026-04-29 removed enum
2026-04-29 fix angle
2026-04-29 removed useless array
2026-04-29 new try
2026-04-29 logic refactoring 1rst draft
2026-05-01 Bluetooth advertising
2026-05-01 Réimplémente MotorHandler. Ajoute une moyenne glissante à applyTorque, modifie la logique de slowShutdown et défini les méthodes initializeMotors et exitMotors
2026-05-04 Now prints out every character received
2026-05-05 Making an interpreter for the bluetooth messages
2026-05-06 Trying to receive data
2026-05-06 Removed test functions that are not needed anymore
2026-05-06 single grounded foot torque revisited
2026-05-07 torque capped in logic
2026-05-08 Added final class file
2026-05-08 HALIMA: bluetooth is now one class
2026-05-09 torque inverted for left leg
2026-05-09 Device name is in class
2026-05-09 hmi comm now in core folder
2026-05-09 Now sends battery level
2026-05-10 fixe semaphore and crabe mode issues
2026-05-10 mutex added to motor state
2026-05-10 multiplier to torque added
2026-05-10 fixed motor handler enums
2026-05-10 testing
2026-05-11 motors only upack their id
2026-05-12 broker for receiving can messages with handler
2026-05-13 test on person (10% motor power)
2026-05-13 fixe merge from HMI_2026
2026-05-13 HMI motor security added
2026-05-15 config headers added
2026-05-15 settings cubemars fixed + tested
2026-06-08 Refactor the motor interface and implementation classes
    The changes were tested on the motors 2026/06/08
2026-06-13 docs: first draft for the code guideline
2026-06-14 Added more robust error handling of Cubemars motors
    Added a getErrorDescription method. Each motor implementation now defines its own error descriptions and its own error enum. getTemperature was renamed getMostfetTemperature to be more accurate. getP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
2026-06-14 Deleted unused dependencies
2026-06-17 Ensures this branch respects the code guidelines
2026-06-17 Replaced the class diagram .svg by a .png because the svg looks ugly on GitHub
2026-06-18 Fixes the motorHandler include in main.cpp
2026-06-18 Updated the class diagram for MotorHandler
